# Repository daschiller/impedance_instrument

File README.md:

# Introduction

Source code and PCB design files for an impedance and temperature measurement
instrument. 

# Hardware

The instrument features a BNC socket for connecting the device under test (DUT).
A standard miniature IEC socket allows the connection of a thermocouple.

The board has been designed in KiCad. You can use it to generate your own
Gerbers.

Here's a partial BOM:

* Impedance IC: AD5933
* Thermocouple IC: MCP9600
* Mux: ADG729

The control terminal is a [Seeed Studio
reTerminal](https://wiki.seeedstudio.com/reTerminal/) which is basically a
Raspberry Pi CM4 with a touchscreen and some other peripherals.

# Software

The software is built as a stage for
[pi-gen](https://github.com/RPi-Distro/pi-gen). Just drop it in and include it.
There's also a stage for the device tree and display driver of the reTerminal
device. Both of these are unfortunately not upstreamed.

After building, the result will be an image that can be directly written to the
device. It will boot straight into the UI. The Qt application runs on a DRM
framebuffer without a display server (EGLFS). The image has been tested with the
64 bit version of Bullseye.

The code does contain some out-of-tree modifications to the AD5933 IIO kernel
driver. It has been extended with variable clock rate support (for low
excitation frequencies). In the default implementation the clock is sourced from
the Raspberry Pi GPCLK peripheral.

Additionally, there's a tiny patch to libiio (included as a binary package in
this repo):
https://lore.kernel.org/all/1204b19a92343a9e3a6ec5df3cef94f6777e08c4.camel@jku.at/

# Manual

There's a manual that can be built with pandoc. Set up a LaTeX environment and
run the following to build a PDF:
```sh
make pdf
```
You can also generate a nice printable booklet using:
```sh
make booklet
```
This requires the `pdfbook2` script which is part of TeX Live and shipped in the
"texlive-extra-utils" package on Debian.

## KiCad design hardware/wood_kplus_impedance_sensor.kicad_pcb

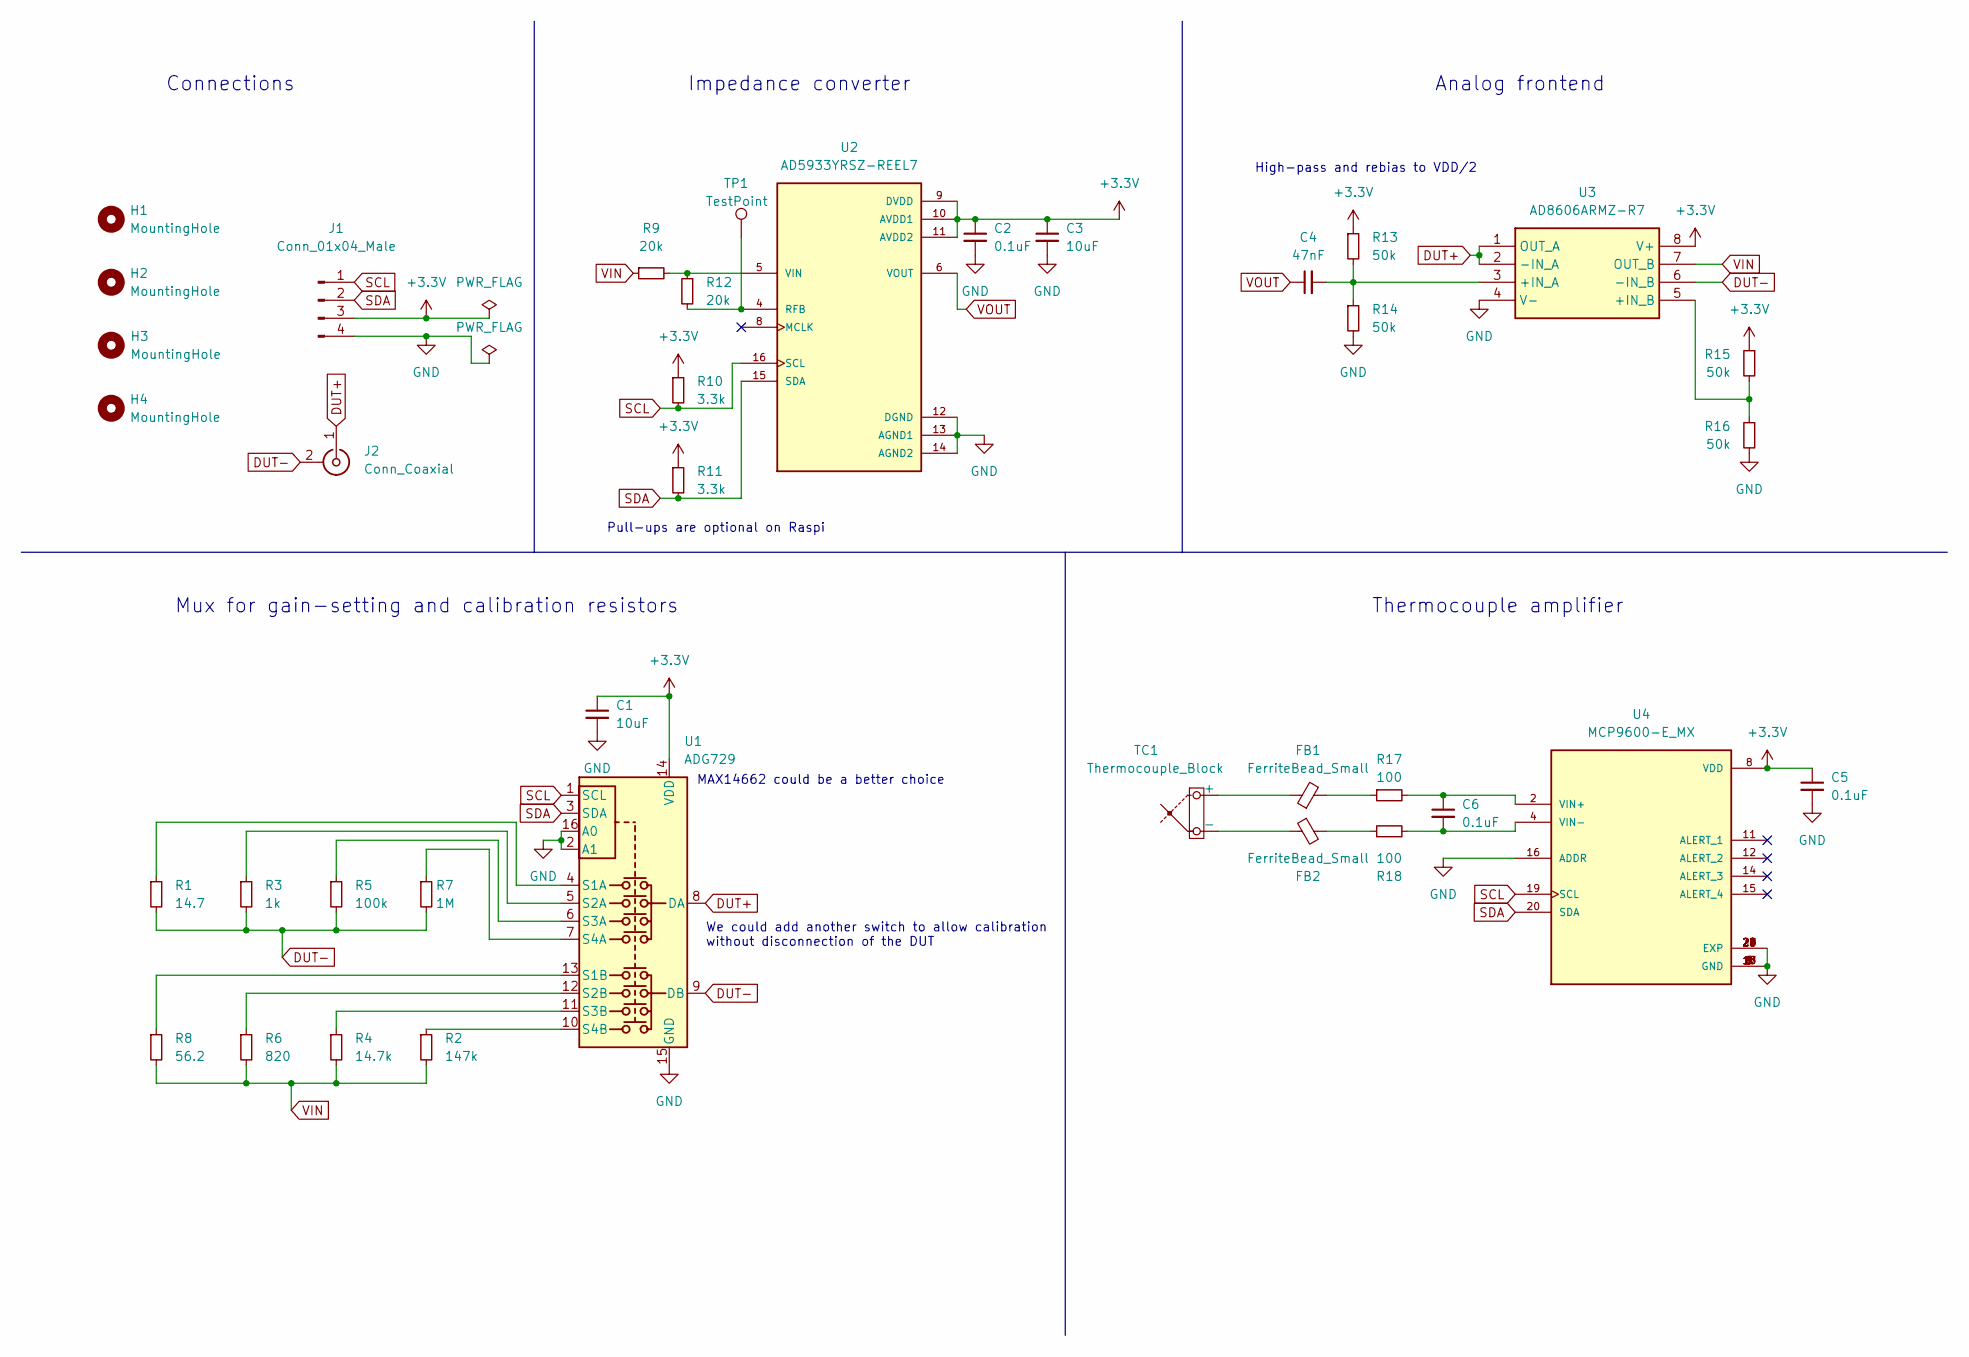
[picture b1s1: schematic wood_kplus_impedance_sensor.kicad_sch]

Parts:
C1, C3: 10uF; C_0603_1608Metric
C2, C5, C6: 0.1uF; C_0603_1608Metric
C4: 47nF; C_0603_1608Metric
FB1, FB2: FerriteBead_Small; L_0603_1608Metric; MPN C1002
H1, H2, H3, H4: MountingHole; MountingHole_3.2mm_M3
J1: Conn_01x04_Male; JST_SH_SM04B-SRSS-TB_1x04-1MP_P1.00mm_Horizontal
J2: Conn_Coaxial; BNC_Amphenol_B6252HB-NPP3G-50_Horizontal
R1: 14.7; R_0603_1608Metric
R2: 147k; R_0603_1608Metric
R3: 1k; R_0603_1608Metric
R4: 14.7k; R_0603_1608Metric
R5: 100k; R_0603_1608Metric
R6: 820; R_0603_1608Metric
R7: 1M; R_0603_1608Metric
R8: 56.2; R_0603_1608Metric
R9, R12: 20k; R_0603_1608Metric
R10, R11: 3.3k; R_0603_1608Metric
R13, R14, R15, R16: 50k; R_0603_1608Metric
R17, R18: 100; R_0603_1608Metric
TC1: Thermocouple_Block; RS_PRO_381-7564
TP1: TestPoint; TestPoint_Pad_D1.5mm
U1: ADG729; TSSOP-16_4.4x5mm_P0.65mm; JLCPCB Rotation Offset 90
U2: AD5933YRSZ-REEL7; SOP65P780X200-16N; PARTREV F; JLCPCB Rotation Offset -90
U3: AD8606ARMZ-R7; SOP65P490X110-8N; Manufacturer_Part_Number AD8606ARMZ-R7; Mouser Part Number 584-AD8606ARMZ-R7
U4: MCP9600-E_MX; QFN65P500X500X100-21N_MCP9600-E_MX; PARTREV F; JLCPCB Rotation Offset -90

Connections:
+3.3V: C1.1, C2.1, C3.1, C5.1, J1.3, R10.1, R11.1, R13.1, R15.1, U1.14 (VDD), U2.9 (DVDD), U2.10 (AVDD1), U2.11 (AVDD2), U3.8 (V+), U4.8 (VDD)
DUT+: J2.1 (In), U1.8 (DA), U3.1 (OUT_A), U3.2 (-IN_A)
DUT-: J2.2 (Ext), R1.2, R3.2, R5.2, R7.2, U1.9 (DB), U3.6 (-IN_B)
GND: C1.2, C2.2, C3.2, C5.2, J1.4, R14.2, R16.2, U1.2 (A1), U1.15 (GND), U1.16 (A0), U2.12 (DGND), U2.13 (AGND1), U2.14 (AGND2), U3.4 (V-), U4.1 (GND), U4.3 (GND), U4.5 (GND), U4.6 (GND), U4.7 (GND), U4.9 (GND), U4.10 (GND), U4.13 (GND), U4.16 (ADDR), U4.17 (GND), U4.18 (GND), U4.21 (EXP), U4.22 (EXP), U4.23 (EXP), U4.24 (EXP), U4.25 (EXP), U4.26 (EXP), U4.27 (EXP), U4.28 (EXP), U4.29 (EXP), U4.30 (EXP)
unnamed: FB1.2, R17.1
unnamed: FB2.2, R18.1
unnamed: FB1.1, TC1.1 (+)
unnamed: FB2.1, TC1.2 (-)
unnamed: R1.1, U1.4 (S1A)
unnamed: R8.1, U1.13 (S1B)
unnamed: R3.1, U1.5 (S2A)
unnamed: R6.1, U1.12 (S2B)
unnamed: R5.1, U1.6 (S3A)
unnamed: R4.1, U1.11 (S3B)
unnamed: R7.1, U1.7 (S4A)
unnamed: R2.1, U1.10 (S4B)
unnamed: R12.2, TP1.1, U2.4 (RFB)
unnamed: R9.2, R12.1, U2.5 (VIN)
unnamed: C4.2, R13.2, R14.1, U3.3 (+IN_A)
unnamed: R15.2, R16.1, U3.5 (+IN_B)
unnamed: C6.1, R17.2, U4.2 (VIN+)
unnamed: C6.2, R18.2, U4.4 (VIN-)
SCL: J1.1, R10.2, U1.1 (SCL), U2.16 (SCL), U4.19 (SCL)
SDA: J1.2, R11.2, U1.3 (SDA), U2.15 (SDA), U4.20 (SDA)
VIN: R2.2, R4.2, R6.2, R8.2, R9.1, U3.7 (OUT_B)
VOUT: C4.1, U2.6 (VOUT)

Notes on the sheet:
Mux for gain-setting and calibration resistors
MAX14662 could be a better choice
Pull-ups are optional on Raspi
Thermocouple amplifier
High-pass and rebias to VDD/2
We could add another switch to allow calibration without disconnection of the DUT
Analog frontend
Impedance converter
Connections

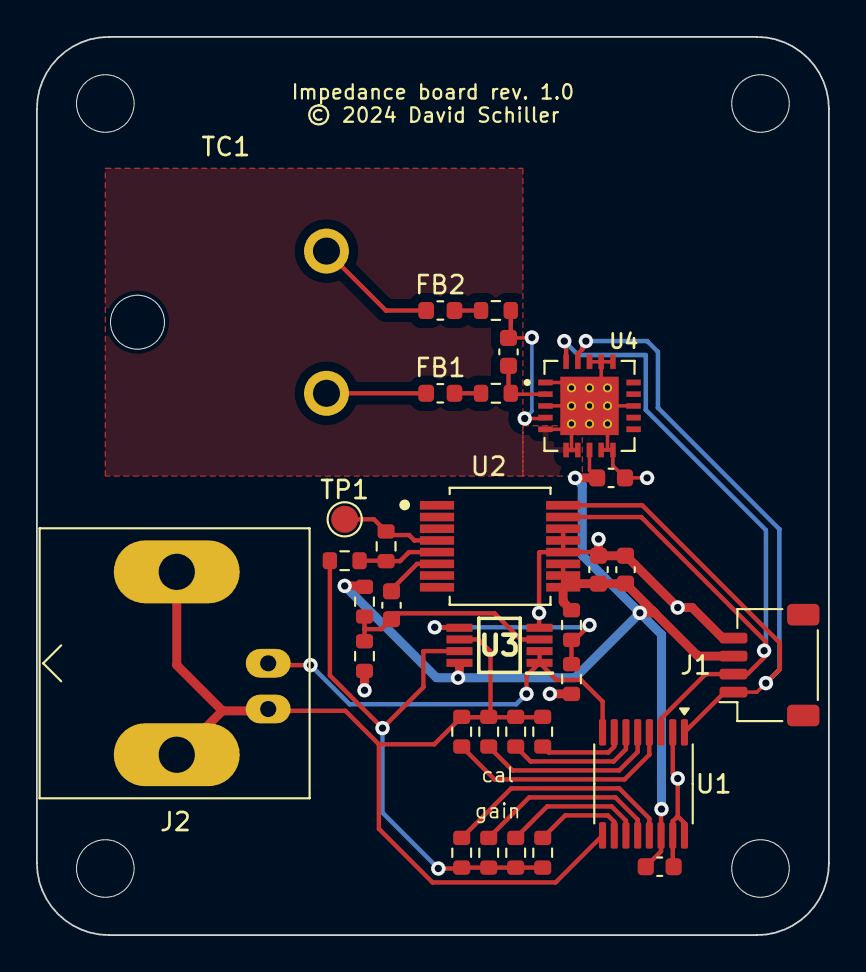
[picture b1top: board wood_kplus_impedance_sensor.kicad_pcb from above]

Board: 2 copper layers, 44.0 x 49.9 mm, 36 parts (0 on the bottom side), 26 nets.

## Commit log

2025-04-09 Add screenshot

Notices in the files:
hardware/wood_kplus_impedance_sensor.kicad_pcb:
© 2024 David Schiller
